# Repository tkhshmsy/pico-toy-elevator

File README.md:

# pico-toy-elevator

This is a toy that imitates the operation of Elevator.

My son loves Elevators, going up and down for hours, and watching YouTube about it every day.  
I hope he enjoys this...

## Features
* LCD displays floors and operations
* Pressed button is lights up
* Speak according to the movement of the elevator ( in Japanese ! )
* All parts are able to get from [Akizuki Denshi](https://akizukidenshi.com/catalog/default.aspx).
* Use Raspberry Pi Pico with Rust language.

## Schematic and Layout

## Bill Of Materials
|Ref|Name|Qty|Description|Link|
|---|----|---|-----------|----|
|U1|RaspberryPi Pico|1|Micro Controller|[https://akizukidenshi.com/catalog/g/g116132/](https://akizukidenshi.com/catalog/g/g116132/) or [https://akizukidenshi.com/catalog/g/g118085/](https://akizukidenshi.com/catalog/g/g118085/)|
|U2|OLED|1|i2c, 0.96inch|[https://akizukidenshi.com/catalog/g/g112031/](https://akizukidenshi.com/catalog/g/g112031/)|
|U3|Aques Talk Pico|1|ATMega328P|[https://akizukidenshi.com/catalog/g/g109973/](https://akizukidenshi.com/catalog/g/g109973/)|
|BT1|Battery holder|1|2xAAA|[https://akizukidenshi.com/catalog/g/g110197/](https://akizukidenshi.com/catalog/g/g110197/)|
|C1,C2,C3,C4,C5,C6,C7,C8,C9,C10,C12,C13|Capacitor|12|0.1uF|[https://akizukidenshi.com/catalog/g/g115927/](https://akizukidenshi.com/catalog/g/g115927/)|
|C11|Capacitor polar|1|100uF|[https://akizukidenshi.com/catalog/g/g105002/](https://akizukidenshi.com/catalog/g/g105002/)|
|LS1|Speaker|1|8ohm 0.5W|[https://akizukidenshi.com/catalog/g/g109797/](https://akizukidenshi.com/catalog/g/g109797/)|
|Q1|2SC1815|1||[https://akizukidenshi.com/catalog/g/g106475/](https://akizukidenshi.com/catalog/g/g106475/)|
|R1,R2,R3,R4,R5,R6,R7,R8,R9,R10|Resistor 220|10|LED limit||
|R11,R13|Resistor 10K|2|Pull up||
|R12|Resistor 270|1|Speaker drive||
|SW1,SW2,SW3,SW4,SW5,SW6,SW7,SW8,SW9,SW10|Push Switch with LED|10|select any color|Green [https://akizukidenshi.com/catalog/g/g102009/](https://akizukidenshi.com/catalog/g/g102009/) Red [https://akizukidenshi.com/catalog/g/g102010](https://akizukidenshi.com/catalog/g/g102010) Yellow [https://akizukidenshi.com/catalog/g/g115372](https://akizukidenshi.com/catalog/g/g115372)|
|SW11|Slide Switch|1|Power SW|[https://akizukidenshi.com/catalog/g/g115707/](https://akizukidenshi.com/catalog/g/g115707/)|
|Y1|Resonator|1|16MHz|[https://akizukidenshi.com/catalog/g/g109576/](https://akizukidenshi.com/catalog/g/g109576/)|

## License
* MIT

## Author
* tkhshmsy@gmail.com

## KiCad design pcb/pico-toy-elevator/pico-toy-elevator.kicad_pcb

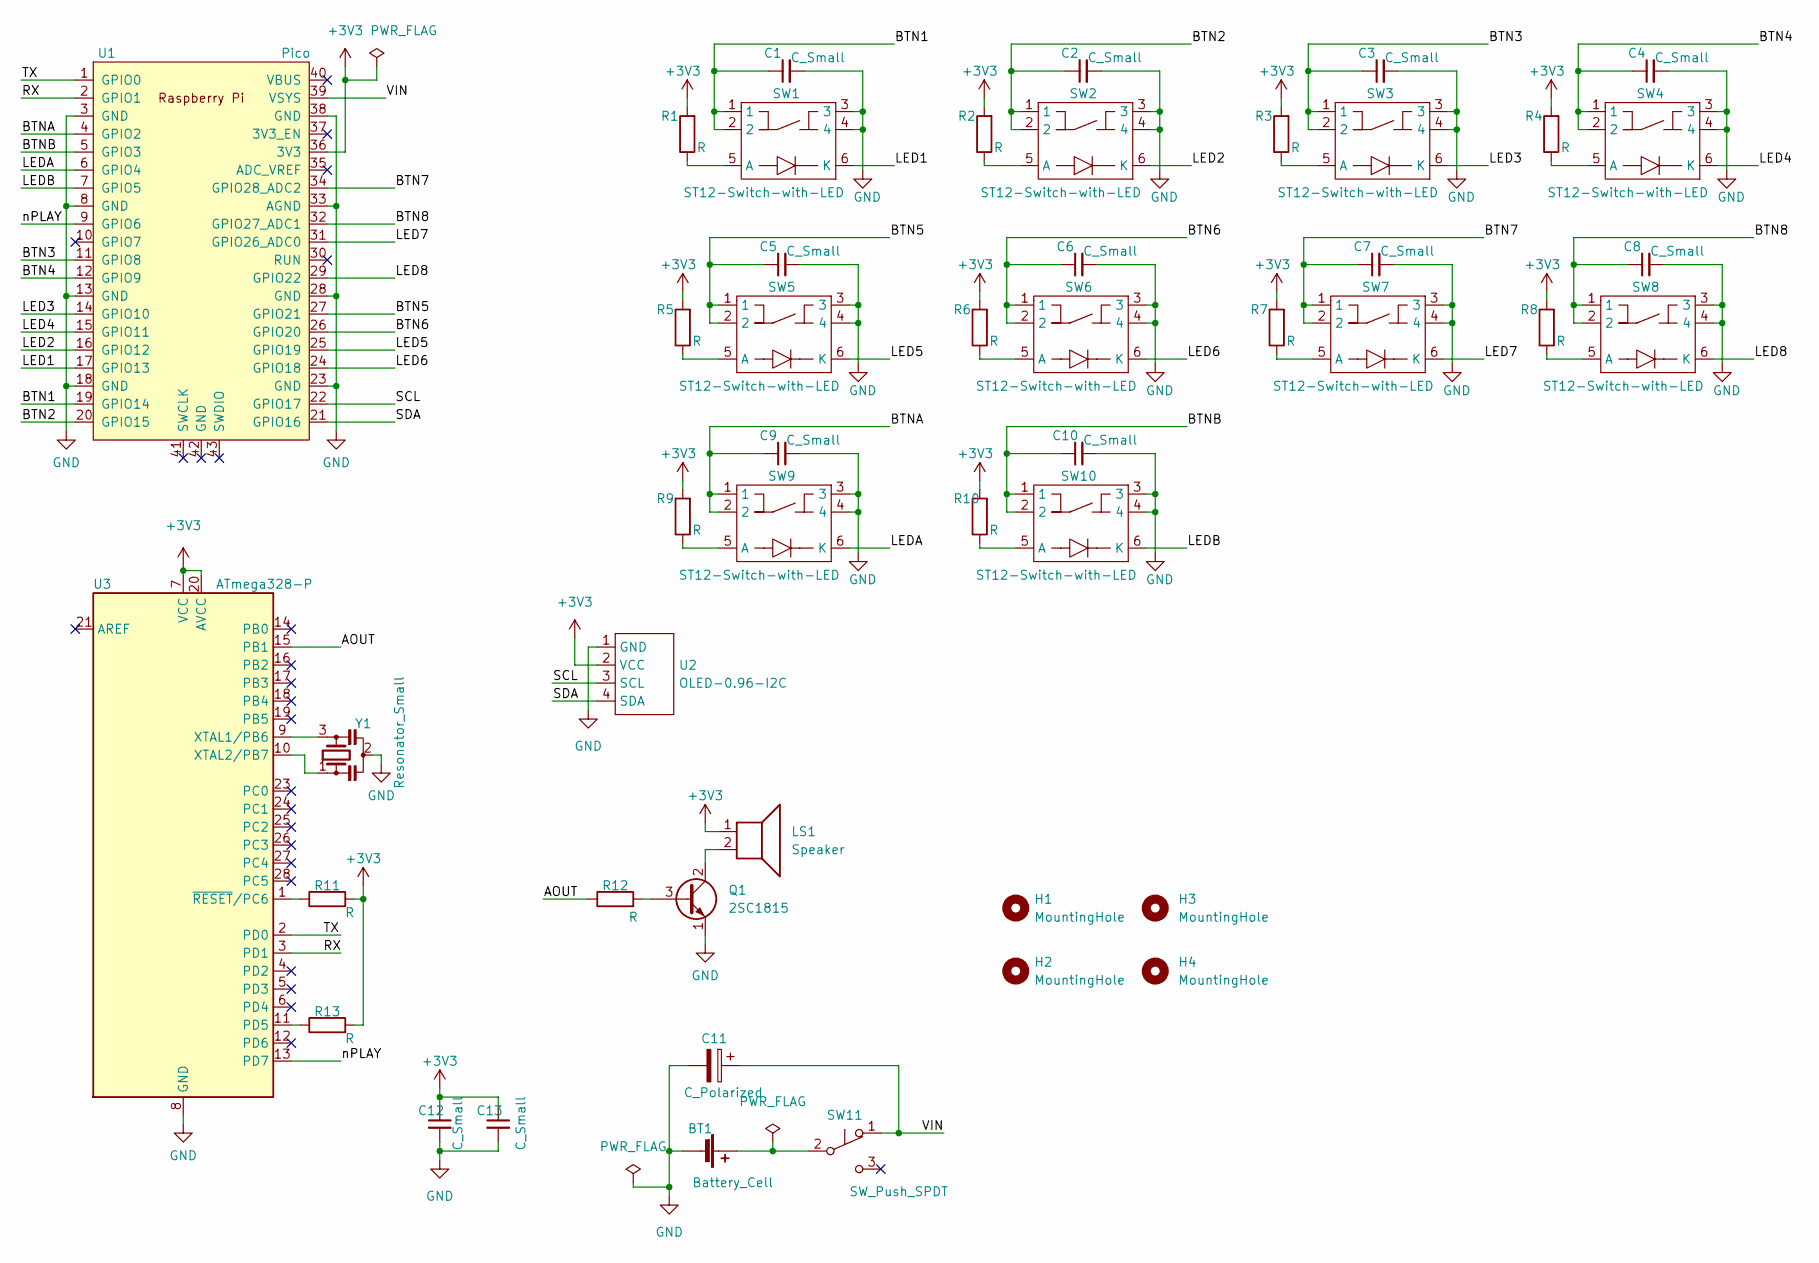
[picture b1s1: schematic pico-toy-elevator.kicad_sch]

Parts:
BT1: Battery_Cell; BH-321-2P24
C1, C2, C3, C4, C5, C6, C7, C8, C9, C10, C12, C13: C_Small; C_Rect_L4.0mm_W2.5mm_P2.50mm
C11: C_Polarized; CP_Radial_D5.0mm_P2.50mm
H1, H2, H3, H4: MountingHole; MountingHole_3.2mm_M3_Pad
LS1: Speaker; UGSM23A
Q1: 2SC1815; TO-92_Inline
R1, R2, R3, R4, R5, R6, R7, R8, R9, R10, R11, R12, R13: R; R_Axial_DIN0204_L3.6mm_D1.6mm_P5.08mm_Horizontal
SW1, SW2, SW3, SW4, SW5, SW6, SW7, SW8, SW9, SW10: ST12-Switch-with-LED; ST12
SW11: SW_Push_SPDT; SS-12D00G3
U1: Pico; RPi_Pico_SMD_TH
U2: OLED-0.96-I2C
U3: ATmega328-P; DIP-28_W7.62mm
Y1: Resonator_Small; Crystal_HC49-U-3Pin_Vertical

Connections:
+3V3: C12.1, C13.1, LS1.1, R1.2, R2.2, R3.2, R4.2, R5.2, R6.2, R7.2, R8.2, R9.2, R10.2, R11.2, R13.2, U1.36 (3V3), U2.2 (VCC), U3.7 (VCC), U3.20 (AVCC)
/AOUT: R12.1, U3.15 (PB1)
/BTN1: C1.1, SW1.1, SW1.2, U1.19 (GPIO14)
/BTN2: C2.1, SW2.1, SW2.2, U1.20 (GPIO15)
/BTN3: C3.1, SW3.1, SW3.2, U1.11 (GPIO8)
/BTN4: C4.1, SW4.1, SW4.2, U1.12 (GPIO9)
/BTN5: C5.1, SW5.1, SW5.2, U1.27 (GPIO21)
/BTN6: C6.1, SW6.1, SW6.2, U1.26 (GPIO20)
/BTN7: C7.1, SW7.1, SW7.2, U1.34 (GPIO28_ADC2)
/BTN8: C8.1, SW8.1, SW8.2, U1.32 (GPIO27_ADC1)
/BTNA: C9.1, SW9.1, SW9.2, U1.4 (GPIO2)
/BTNB: C10.1, SW10.1, SW10.2, U1.5 (GPIO3)
/LED1: SW1.6 (K), U1.17 (GPIO13)
/LED2: SW2.6 (K), U1.16 (GPIO12)
/LED3: SW3.6 (K), U1.14 (GPIO10)
/LED4: SW4.6 (K), U1.15 (GPIO11)
/LED5: SW5.6 (K), U1.25 (GPIO19)
/LED6: SW6.6 (K), U1.24 (GPIO18)
/LED7: SW7.6 (K), U1.31 (GPIO26_ADC0)
/LED8: SW8.6 (K), U1.29 (GPIO22)
/LEDA: SW9.6 (K), U1.6 (GPIO4)
/LEDB: SW10.6 (K), U1.7 (GPIO5)
/RX: U1.2 (GPIO1), U3.3 (PD1)
/SCL: U1.22 (GPIO17), U2.3 (SCL)
/SDA: U1.21 (GPIO16), U2.4 (SDA)
/TX: U1.1 (GPIO0), U3.2 (PD0)
/VIN: C11.1, SW11.1 (A), U1.39 (VSYS)
/nPLAY: U1.9 (GPIO6), U3.13 (PD7)
GND: BT1.2 (-), C1.2, C2.2, C3.2, C4.2, C5.2, C6.2, C7.2, C8.2, C9.2, C10.2, C11.2, C12.2, C13.2, Q1.1 (E), SW1.3, SW1.4, SW2.3, SW2.4, SW3.3, SW3.4, SW4.3, SW4.4, SW5.3, SW5.4, SW6.3, SW6.4, SW7.3, SW7.4, SW8.3, SW8.4, SW9.3, SW9.4, SW10.3, SW10.4, U1.3 (GND), U1.8 (GND), U1.13 (GND), U1.18 (GND), U1.23 (GND), U1.28 (GND), U1.33 (AGND), U1.38 (GND), U2.1 (GND), U3.8 (GND), U3.22 (GND), Y1.2
unnamed: BT1.1 (+), SW11.2 (B)
unnamed: LS1.2, Q1.2 (C)
unnamed: Q1.3 (B), R12.2
unnamed: R1.1, SW1.5 (A)
unnamed: R2.1, SW2.5 (A)
unnamed: R3.1, SW3.5 (A)
unnamed: R4.1, SW4.5 (A)
unnamed: R5.1, SW5.5 (A)
unnamed: R6.1, SW6.5 (A)
unnamed: R7.1, SW7.5 (A)
unnamed: R8.1, SW8.5 (A)
unnamed: R9.1, SW9.5 (A)
unnamed: R10.1, SW10.5 (A)
unnamed: R11.1, U3.1 (~RESET/PC6)
unnamed: R13.1, U3.11 (PD5)
unnamed: U3.9 (XTAL1/PB6), Y1.3
unnamed: U3.10 (XTAL2/PB7), Y1.1

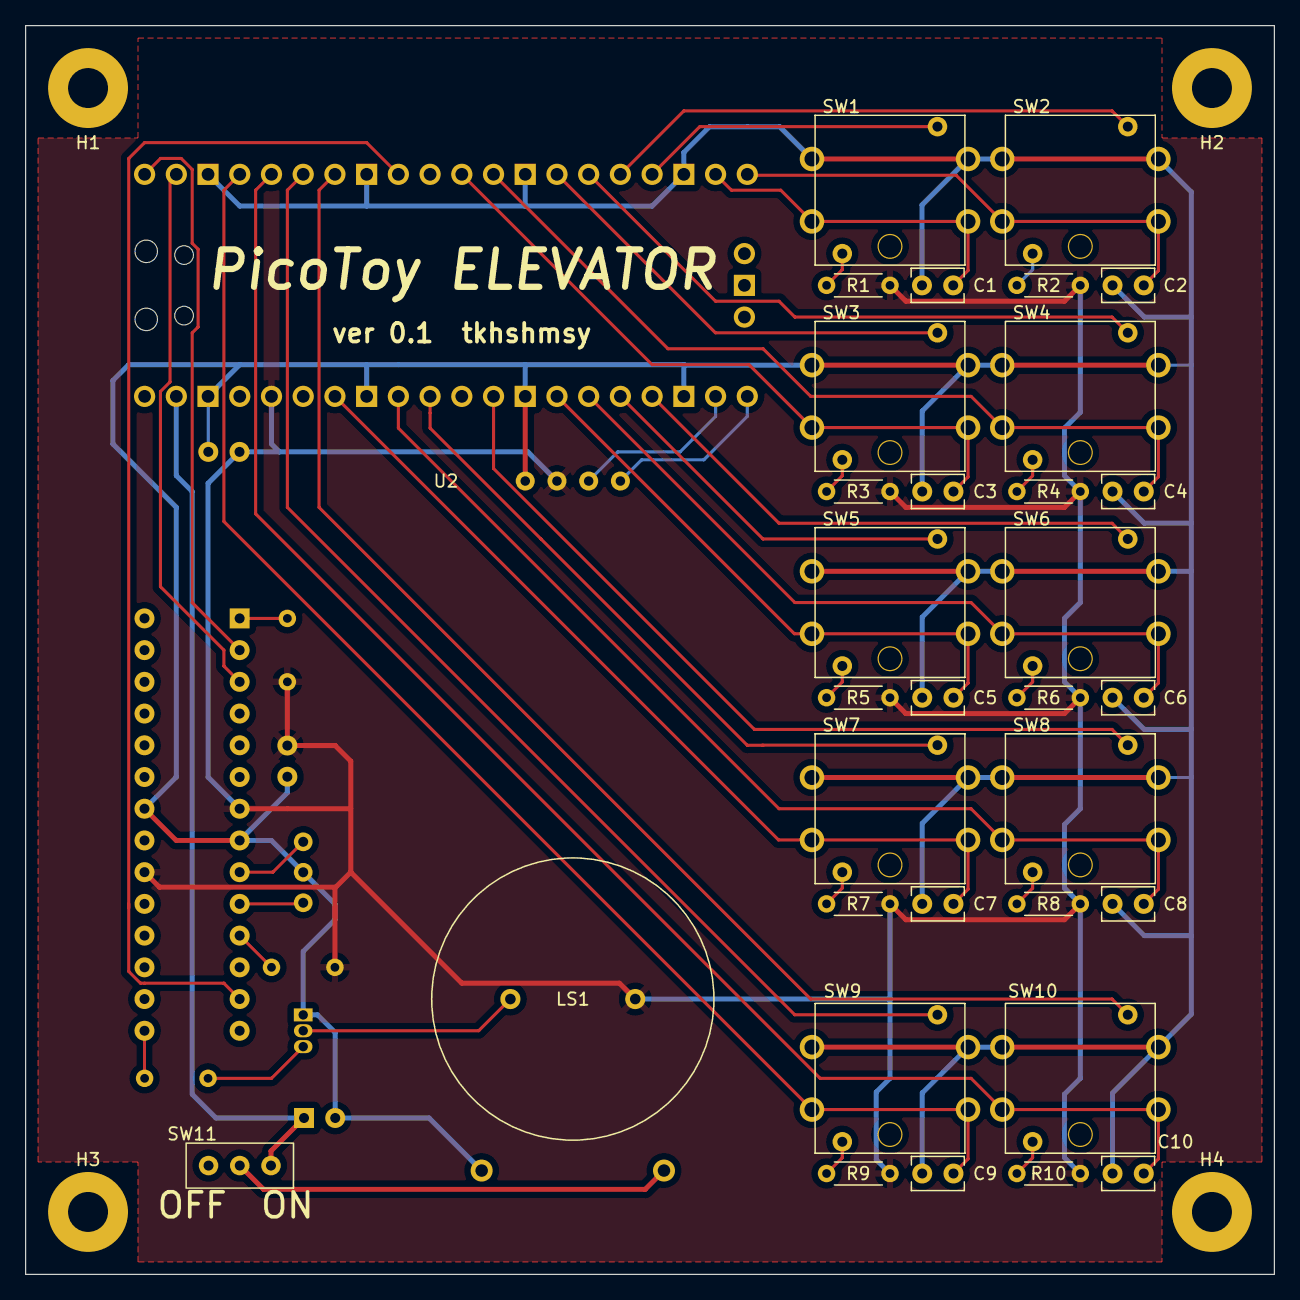
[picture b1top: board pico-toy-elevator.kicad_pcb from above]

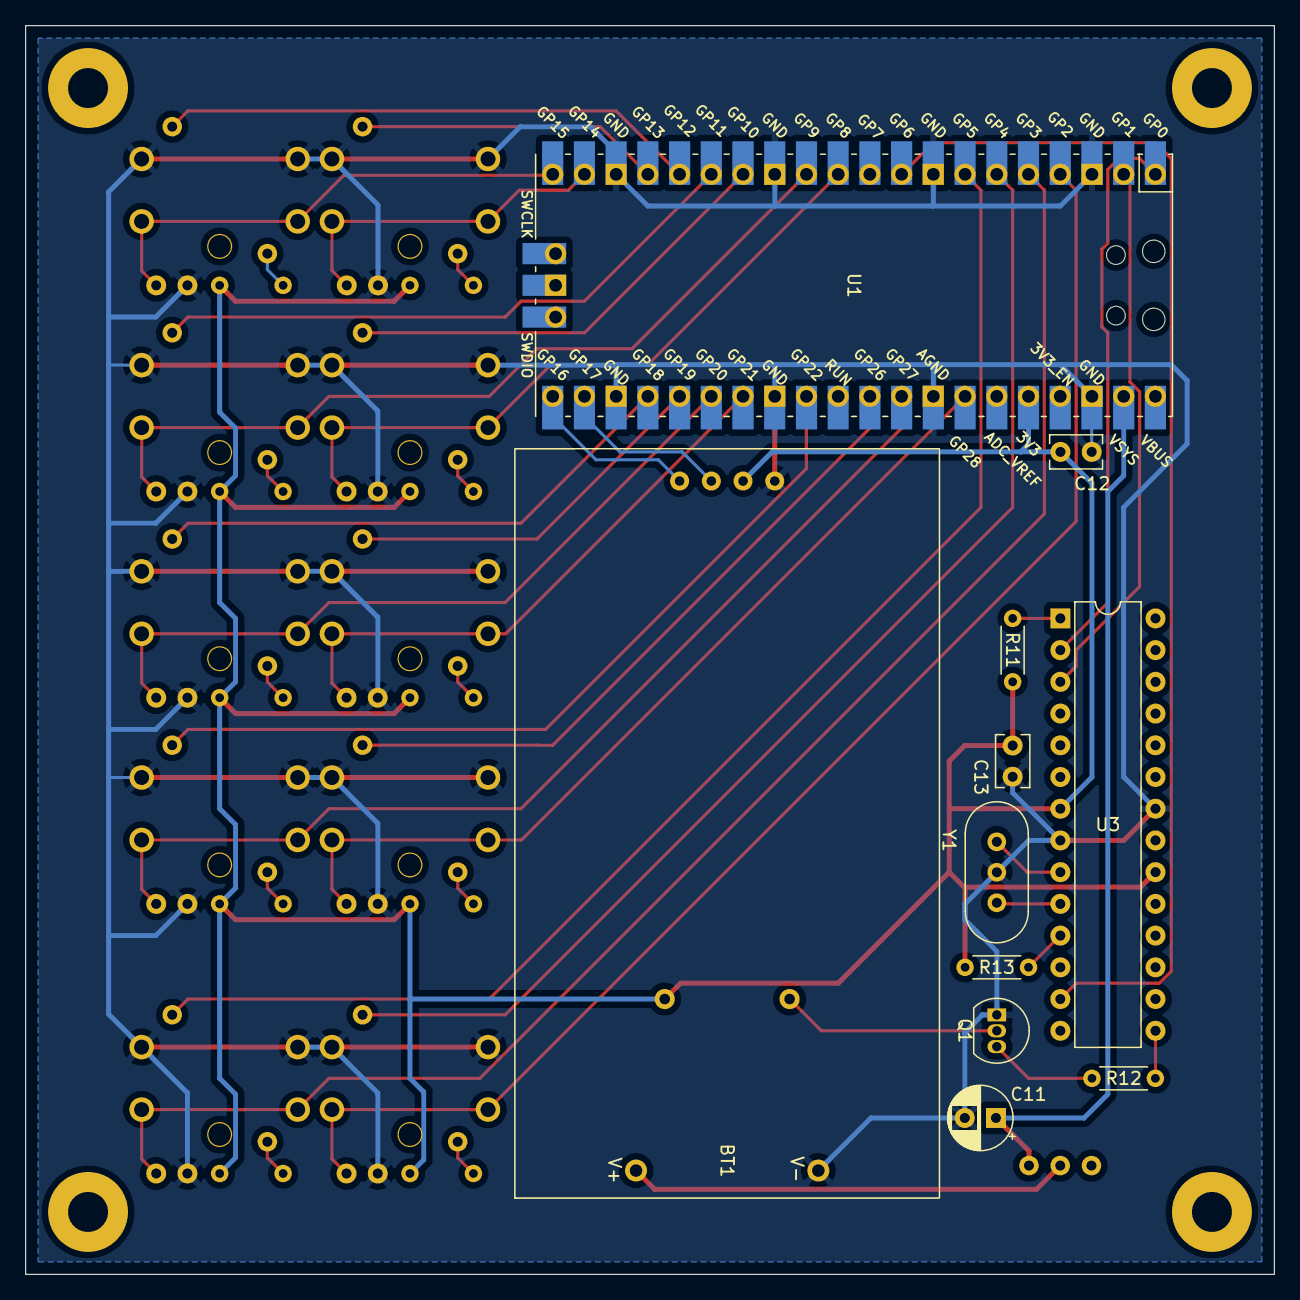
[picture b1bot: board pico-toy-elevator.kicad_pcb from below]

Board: 2 copper layers, 100.0 x 100.0 mm, 48 parts (11 on the bottom side), 46 nets.

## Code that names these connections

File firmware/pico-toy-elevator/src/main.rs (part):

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    let mut led_pin = pins.led.into_push_pull_output();

    // GPIO
    let btn_a = pins.gpio2.into_pull_up_input();
    let btn_b = pins.gpio3.into_pull_up_input();
    let mut led_a = pins.gpio4.into_push_pull_output();
    let mut led_b = pins.gpio5.into_push_pull_output();
    let nplay = pins.gpio6.into_pull_up_input();
    //gpio7 is unused
    let btn_3 = pins.gpio8.into_pull_up_input();
    let btn_4 = pins.gpio9.into_pull_up_input();
    let mut led_3 = pins.gpio10.into_push_pull_output();
    let mut led_4 = pins.gpio11.into_push_pull_output();
    let mut led_2 = pins.gpio12.into_push_pull_output();
    let mut led_1 = pins.gpio13.into_push_pull_output();
    let btn_1 = pins.gpio14.into_pull_up_input();
    let btn_2 = pins.gpio15.into_pull_up_input();
    let mut led_6 = pins.gpio18.into_push_pull_output();
    let mut led_5 = pins.gpio19.into_push_pull_output();
    let btn_6 = pins.gpio20.into_pull_up_input();
    let btn_5 = pins.gpio21.into_pull_up_input();
    let mut led_8 = pins.gpio22.into_push_pull_output();
    let mut led_7 = pins.gpio26.into_push_pull_output();
    let btn_8 = pins.gpio27.into_pull_up_input();
    let btn_7 = pins.gpio28.into_pull_up_input();
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    delay.delay_ms(1000);

    // UART0
    let uart_pins = (pins.gpio0.into_function(), pins.gpio1.into_function());
    let uart0 = bsp::hal::uart::UartPeripheral::new(pac.UART0, uart_pins, &mut pac.RESETS)
        .enable(
            UartConfig::new(9600.Hz(), DataBits::Eight, None, StopBits::One),
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        .unwrap();

    // I2C0
    // let i2c_pins = (pins.gpio16.into_function(), pins.gpio17.into_function());
    let sda_pin = pins.gpio16.into_function();
    let scl_pin = pins.gpio17.into_function();
    let i2c = bsp::hal::I2C::i2c0(
        pac.I2C0,
        sda_pin,
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
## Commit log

2024-01-09 Initial Commit with PCB v 0.1
2024-01-21 fix PCB
2024-02-19 Add firmware
2024-02-20 Add README
